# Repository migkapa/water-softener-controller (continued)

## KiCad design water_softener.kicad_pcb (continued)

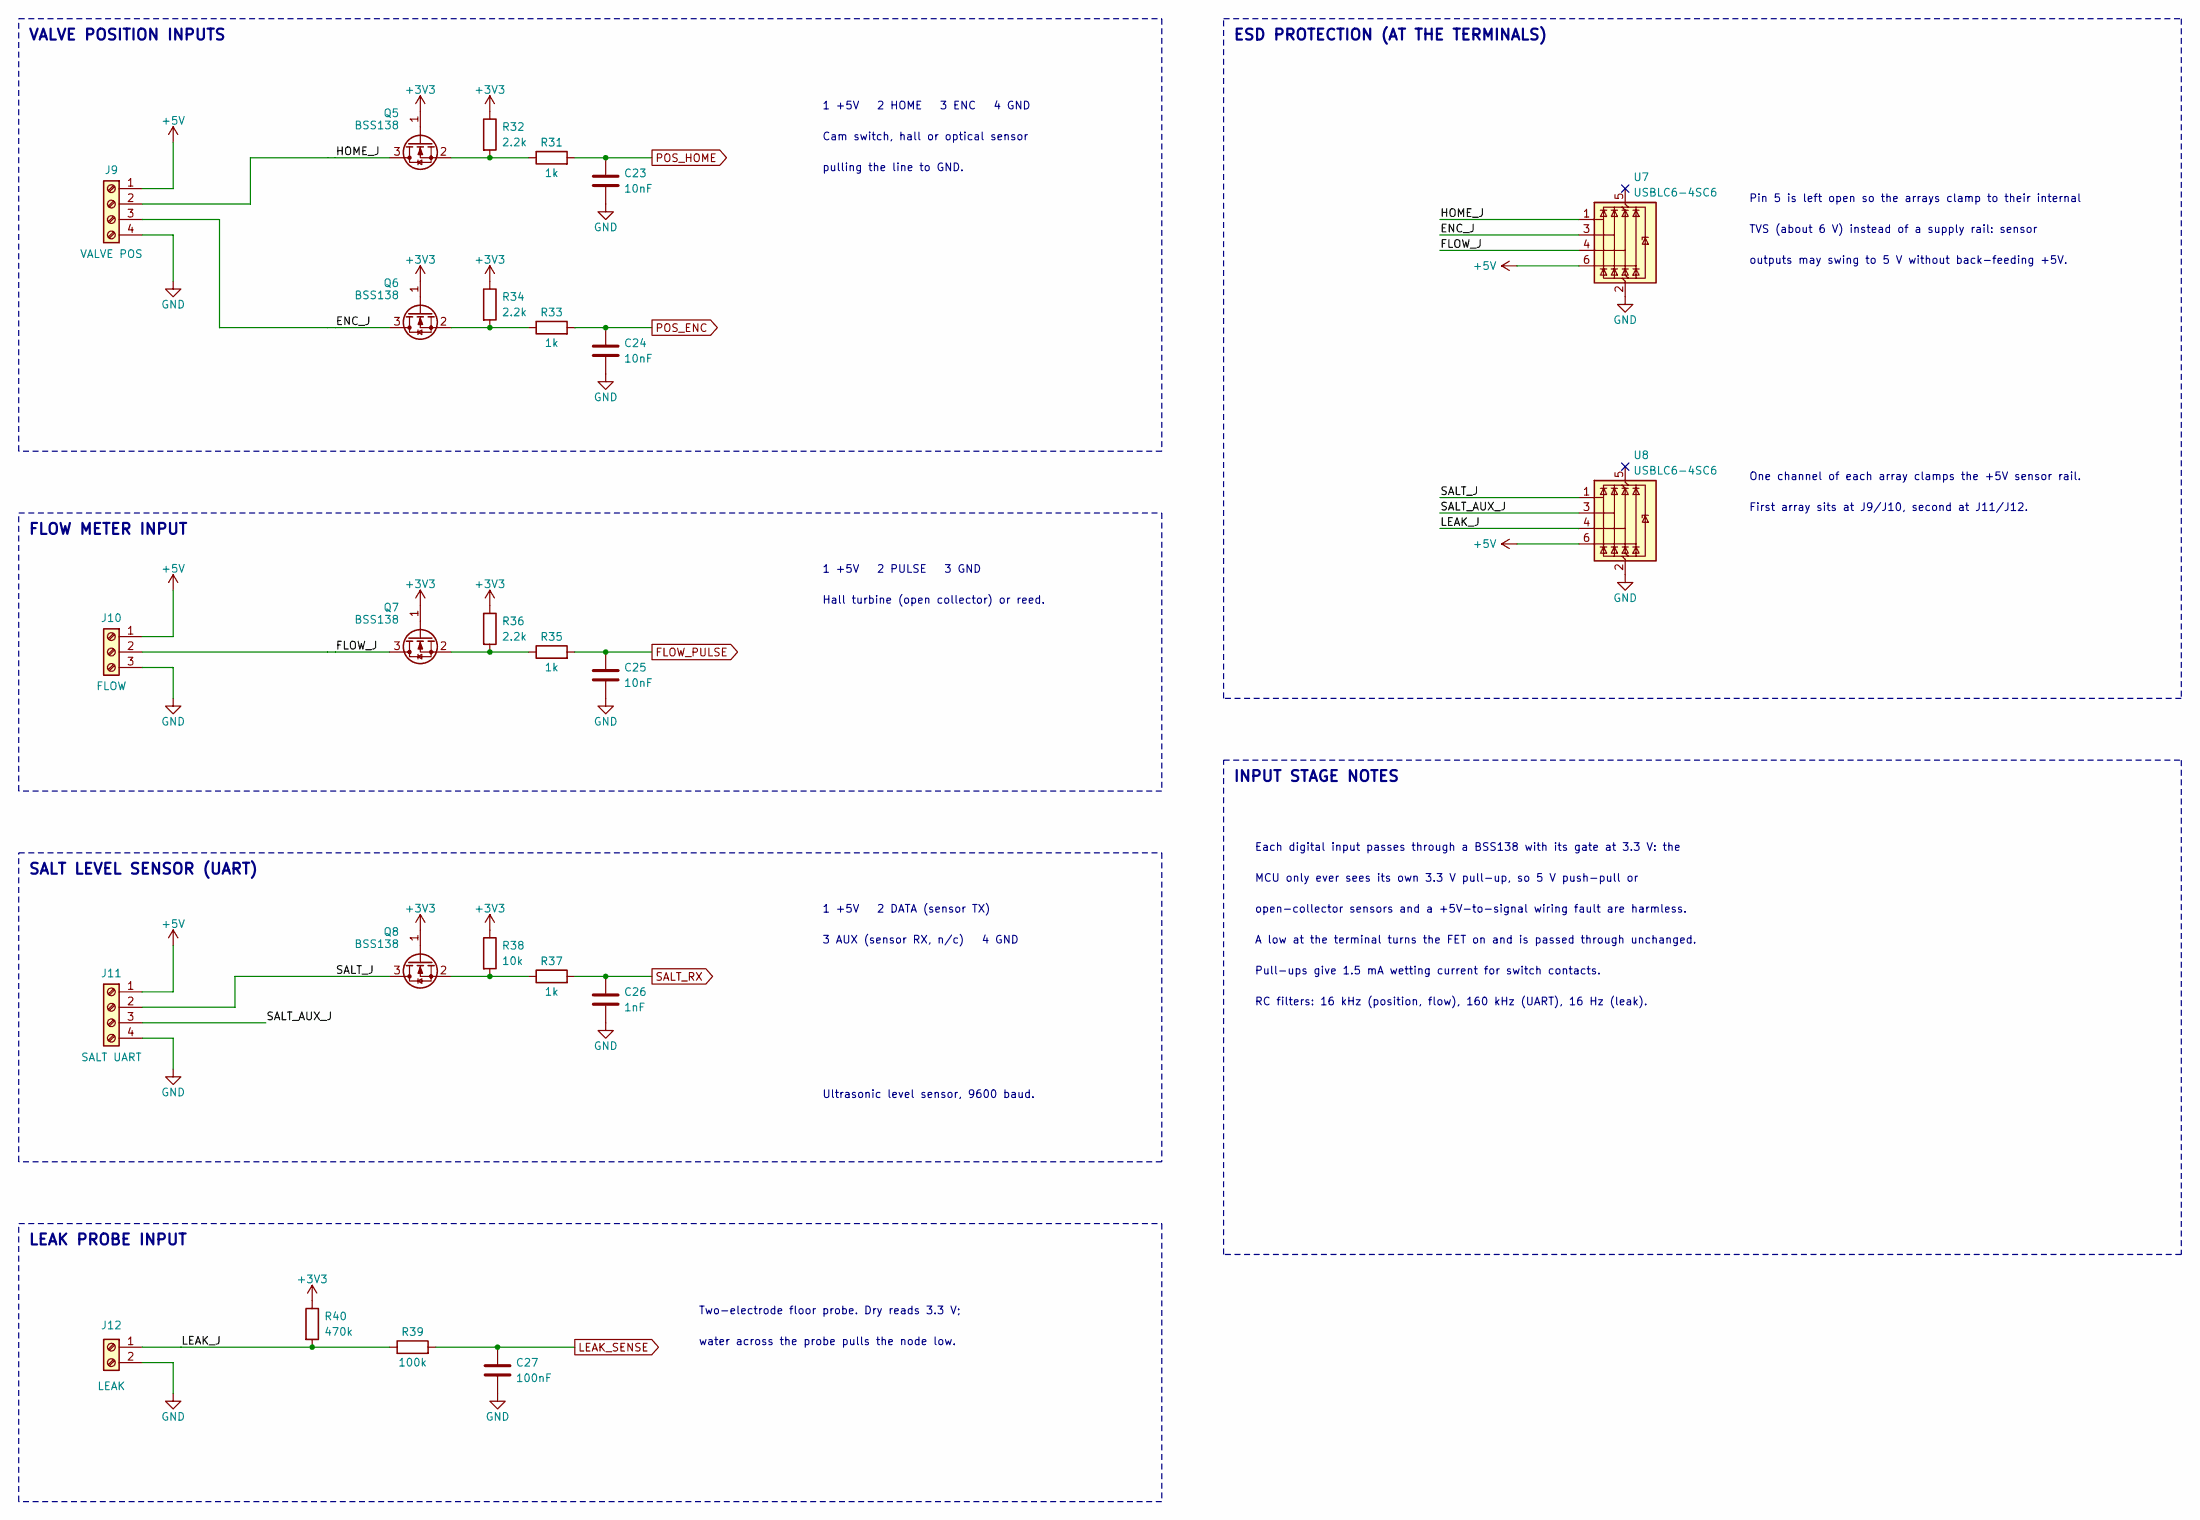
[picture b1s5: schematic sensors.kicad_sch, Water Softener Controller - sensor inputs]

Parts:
C23, C24, C25: 10nF; C_0603_1608Metric; Rating 50 V X7R
C26: 1nF; C_0603_1608Metric; Rating 50 V X7R
C27: 100nF; C_0603_1608Metric; Rating 50 V X7R
J9: VALVE POS; PhoenixContact_MC_1,5_4-G-3.5_1x04_P3.50mm_Horizontal; MPN 1844236
J10: FLOW; PhoenixContact_MC_1,5_3-G-3.5_1x03_P3.50mm_Horizontal; MPN 1844223
J11: SALT UART; PhoenixContact_MC_1,5_4-G-3.5_1x04_P3.50mm_Horizontal; MPN 1844236
J12: LEAK; PhoenixContact_MC_1,5_2-G-3.5_1x02_P3.50mm_Horizontal; MPN 1844210
Q5, Q6, Q7, Q8: BSS138; SOT-23; MPN BSS138
R31, R33, R35, R37: 1k; R_0603_1608Metric; Rating 1% 0.1W
R32, R34, R36: 2.2k; R_0603_1608Metric; Rating 1% 0.1W
R38: 10k; R_0603_1608Metric; Rating 1% 0.1W
R39: 100k; R_0603_1608Metric; Rating 1% 0.1W
R40: 470k; R_0603_1608Metric; Rating 1% 0.1W
U7, U8: USBLC6-4SC6; SOT-23-6; MPN USBLC6-4SC6

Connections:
+3V3: Q5.1 (G), Q6.1 (G), Q7.1 (G), Q8.1 (G), R32.1, R34.1, R36.1, R38.1, R40.1; also elsewhere on the board
+5V: J9.1, J10.1, J11.1, U7.6 (I/O4), U8.6 (I/O4); also elsewhere on the board
/Sensors/ENC_J: J9.3, Q6.3 (D), U7.3 (I/O2)
/Sensors/FLOW_J: J10.2, Q7.3 (D), U7.4 (I/O3)
/Sensors/HOME_J: J9.2, Q5.3 (D), U7.1 (I/O1)
/Sensors/LEAK_J: J12.1, R39.1, R40.2, U8.4 (I/O3)
/Sensors/SALT_AUX_J: J11.3, U8.3 (I/O2)
/Sensors/SALT_J: J11.2, Q8.3 (D), U8.1 (I/O1)
FLOW_PULSE: C25.1, R35.2; also elsewhere on the board
GND: C23.2, C24.2, C25.2, C26.2, C27.2, J9.4, J10.3, J11.4, J12.2, U7.2 (GND), U8.2 (GND); also elsewhere on the board
LEAK_SENSE: C27.1, R39.2; also elsewhere on the board
unnamed: Q5.2 (S), R31.1, R32.2
unnamed: Q6.2 (S), R33.1, R34.2
unnamed: Q7.2 (S), R35.1, R36.2
unnamed: Q8.2 (S), R37.1, R38.2
POS_ENC: C24.1, R33.2; also elsewhere on the board
POS_HOME: C23.1, R31.2; also elsewhere on the board
SALT_RX: C26.1, R37.2; also elsewhere on the board

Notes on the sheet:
3 AUX (sensor RX, n/c) 4 GND
FLOW METER INPUT
INPUT STAGE NOTES
Pin 5 is left open so the arrays clamp to their internal
open-collector sensors and a +5V-to-signal wiring fault are harmless.
MCU only ever sees its own 3.3 V pull-up, so 5 V push-pull or
TVS (about 6 V) instead of a supply rail: sensor
VALVE POSITION INPUTS
Each digital input passes through a BSS138 with its gate at 3.3 V: the
1 +5V 2 HOME 3 ENC 4 GND
RC filters: 16 kHz (position, flow), 160 kHz (UART), 16 Hz (leak).
First array sits at J9/J10, second at J11/J12.
water across the probe pulls the node low.
A low at the terminal turns the FET on and is passed through unchanged.
Hall turbine (open collector) or reed.
1 +5V 2 PULSE 3 GND
Cam switch, hall or optical sensor
Ultrasonic level sensor, 9600 baud.
outputs may swing to 5 V without back-feeding +5V.
1 +5V 2 DATA (sensor TX)
ESD PROTECTION (AT THE TERMINALS)
One channel of each array clamps the +5V sensor rail.
Two-electrode floor probe. Dry reads 3.3 V;
pulling the line to GND.
LEAK PROBE INPUT
SALT LEVEL SENSOR (UART)
Pull-ups give 1.5 mA wetting current for switch contacts.

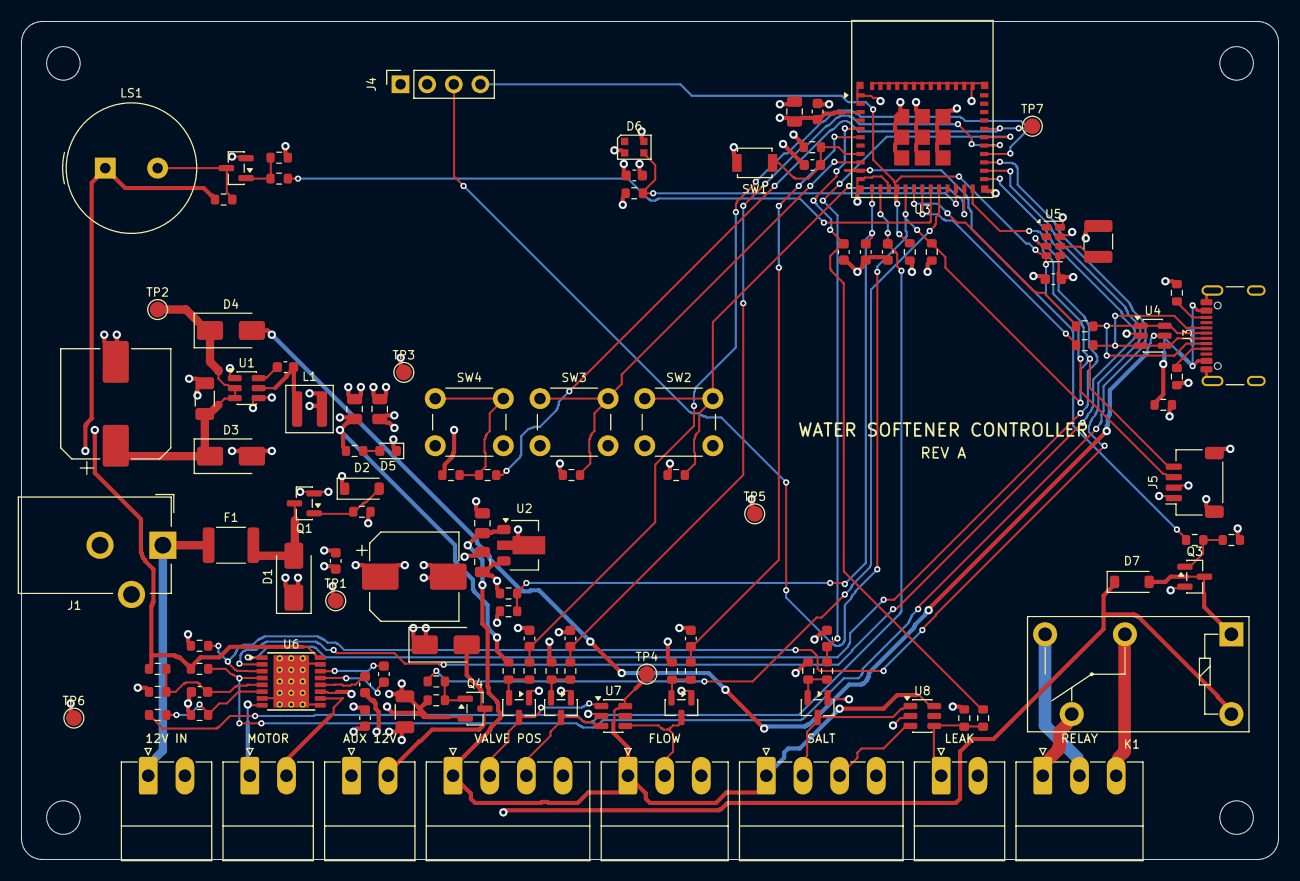
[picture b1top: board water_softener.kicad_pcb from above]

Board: 4 copper layers, 120.0 x 80.0 mm, 122 parts (0 on the bottom side), 67 nets.

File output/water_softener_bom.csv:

"Refs","Value","Rating","Footprint","Manufacturer","MPN","Qty"
"C1","220uF","25 V aluminium, 105 C","Capacitor_SMD:CP_Elec_8x10","Panasonic","EEE-FK1E221P","1"
"C2,C5,C10,C12,C14,C16,C17,C18,C19,C21,C27","100nF","50 V X7R","Capacitor_SMD:C_0603_1608Metric","","","11"
"C3","470uF","25 V aluminium, 105 C","Capacitor_SMD:CP_Elec_10x10","Panasonic","EEE-FK1E471P","1"
"C4,C20","10uF","25 V X7R","Capacitor_SMD:C_1206_3216Metric","","","2"
"C6,C7","22uF","10 V X5R","Capacitor_SMD:C_0805_2012Metric","","","2"
"C8,C9","1uF","50 V X7R","Capacitor_SMD:C_0805_2012Metric","","","2"
"C11","10uF","10 V X5R","Capacitor_SMD:C_0805_2012Metric","","","1"
"C13","1uF","16 V X7R","Capacitor_SMD:C_0603_1608Metric","","","1"
"C15","11mF","3.3 V EDLC","Capacitor_SMD:C_1210_3225Metric","Seiko Instruments","CPH3225A","1"
"C22","22nF","50 V X7R","Capacitor_SMD:C_0603_1608Metric","","","1"
"C23,C24,C25","10nF","50 V X7R","Capacitor_SMD:C_0603_1608Metric","","","3"
"C26","1nF","50 V X7R","Capacitor_SMD:C_0603_1608Metric","","","1"
"D1","SMAJ16CA","16 V standoff, 400 W, bidirectional","Diode_SMD:D_SMA","Littelfuse","SMAJ16CA","1"
"D2","BZT52C10","10 V 5%","Diode_SMD:D_SOD-123","Diodes Inc.","BZT52C10-7-F","1"
"D3,D4,D8","SS14","40 V 1 A Schottky","Diode_SMD:D_SMA","Vishay","SS14-E3/61T","3"
"D5","GREEN","","LED_SMD:LED_0603_1608Metric","Wurth Elektronik","150060GS75000","1"
"D6","WS2812B-2020","","LED_SMD:LED_WS2812B-2020_PLCC4_2.0x2.0mm","Worldsemi","WS2812B-2020 (V6)","1"
"D7","1N4148W","","Diode_SMD:D_SOD-123","Diodes Inc.","1N4148W-7-F","1"
"F1","1.5A / 24V","1.5 A hold, 3 A trip, 24 V","Fuse:Fuse_1812_4532Metric","Bourns","MF-MSMF150/24X-2","1"
"J1","12V DC IN","","Connector_BarrelJack:BarrelJack_CUI_PJ-102AH_Horizontal","CUI Devices","PJ-102AH","1"
"J2","12V IN (ALT)","","Connector_Phoenix_MC:PhoenixContact_MC_1,5_2-G-3.5_1x02_P3.50mm_Horizontal","Phoenix Contact","1844210","1"
"J3","USB-C","","Connector_USB:USB_C_Receptacle_GCT_USB4105-xx-A_16P_TopMnt_Horizontal","GCT","USB4105-GF-A","1"
"J4","OLED","","Connector_PinSocket_2.54mm:PinSocket_1x04_P2.54mm_Vertical","Generic","1x04 2.54 mm socket","1"
"J5","QWIIC","","Connector_JST:JST_SH_SM04B-SRSS-TB_1x04-1MP_P1.00mm_Horizontal","JST","SM04B-SRSS-TB","1"
"J6","VALVE MOTOR","","Connector_Phoenix_MC:PhoenixContact_MC_1,5_2-G-3.5_1x02_P3.50mm_Horizontal","Phoenix Contact","1844210","1"
"J7","RELAY","","Connector_Phoenix_MC:PhoenixContact_MC_1,5_3-G-3.5_1x03_P3.50mm_Horizontal","Phoenix Contact","1844223","1"
"J8","AUX 12V OUT","","Connector_Phoenix_MC:PhoenixContact_MC_1,5_2-G-3.5_1x02_P3.50mm_Horizontal","Phoenix Contact","1844210","1"
"J9","VALVE POS","","Connector_Phoenix_MC:PhoenixContact_MC_1,5_4-G-3.5_1x04_P3.50mm_Horizontal","Phoenix Contact","1844236","1"
"J10","FLOW","","Connector_Phoenix_MC:PhoenixContact_MC_1,5_3-G-3.5_1x03_P3.50mm_Horizontal","Phoenix Contact","1844223","1"
"J11","SALT UART","","Connector_Phoenix_MC:PhoenixContact_MC_1,5_4-G-3.5_1x04_P3.50mm_Horizontal","Phoenix Contact","1844236","1"
"J12","LEAK","","Connector_Phoenix_MC:PhoenixContact_MC_1,5_2-G-3.5_1x02_P3.50mm_Horizontal","Phoenix Contact","1844210","1"
"K1","G5Q-14 DC12","12 V coil 33 mA, SPDT","Relay_THT:Relay_SPDT_Omron-G5Q-1","Omron","G5Q-14 DC12","1"
"L1","4.7uH","4.7 uH, Isat 4.5 A, 44 mOhm","Inductor_SMD:L_Coilcraft_XAL4030-XXX","Coilcraft","XAL4030-472MEC","1"
"LS1","PS1240","","Buzzer_Beeper:Buzzer_TDK_PS1240P02BT_D12.2mm_H6.5mm","TDK","PS1240P02BT","1"
"Q1","DMP3099L","-30 V, 65 mOhm, Vgs +/-20 V","Package_TO_SOT_SMD:SOT-23","Diodes Inc.","DMP3099L-7","1"
"Q2,Q3,Q5,Q6,Q7,Q8","BSS138","","Package_TO_SOT_SMD:SOT-23","onsemi","BSS138","6"
"Q4","AO3400A","","Package_TO_SOT_SMD:SOT-23","Alpha & Omega","AO3400A","1"
"R1,R3,R19,R39","100k","1% 0.1W","Resistor_SMD:R_0603_1608Metric","","","4"
"R2,R8,R31,R33,R35,R37","1k","1% 0.1W","Resistor_SMD:R_0603_1608Metric","","","6"
"R4","15k","1% 0.1W","Resistor_SMD:R_0603_1608Metric","","","1"
"R5,R6,R7,R9,R10,R17,R21,R24,R25,R26,R28,R30,R38","10k","1% 0.1W","Resistor_SMD:R_0603_1608Metric","","","13"
"R11,R12","22R","1% 0.1W","Resistor_SMD:R_0603_1608Metric","","","2"
"R13,R14","5.1k","1% 0.1W","Resistor_SMD:R_0603_1608Metric","","","2"
"R15,R16,R20,R32,R34,R36","2.2k","1% 0.1W","Resistor_SMD:R_0603_1608Metric","","","6"
"R18,R27,R29","100R","1% 0.1W","Resistor_SMD:R_0603_1608Metric","","","3"
"R22","30.1k","1% 0.1W","Resistor_SMD:R_0603_1608Metric","","","1"
"R23","2.49k","1% 0.1W","Resistor_SMD:R_0603_1608Metric","","","1"
"R40","470k","1% 0.1W","Resistor_SMD:R_0603_1608Metric","","","1"
"SW1","RESET","","Button_Switch_SMD:SW_SPST_B3U-1000P","Omron","B3U-1000P","1"
"SW2","SET / BOOT","","Button_Switch_THT:SW_PUSH_6mm","Omron","B3F-1000","1"
"SW3","UP","","Button_Switch_THT:SW_PUSH_6mm","Omron","B3F-1000","1"
"SW4","DOWN","","Button_Switch_THT:SW_PUSH_6mm","Omron","B3F-1000","1"
"U1","AP63203WU","","Package_TO_SOT_SMD:TSOT-23-6","Diodes Inc.","AP63203WU-7","1"
"U2","L78L05","","Package_TO_SOT_SMD:SOT-89-3","STMicroelectronics","L78L05ABUTR","1"
"U3","ESP32-C6-MINI-1-N4","","RF_Module:ESP32-C6-MINI-1","Espressif","ESP32-C6-MINI-1-N4","1"
"U4","USBLC6-2SC6","","Package_TO_SOT_SMD:SOT-23-6","STMicroelectronics","USBLC6-2SC6","1"
"U5","RV-3028-C7","","Package_SON:MicroCrystal_C7_SON-8_1.5x3.2mm_P0.9mm","Micro Crystal","RV-3028-C7 32.768kHz 1ppm TA QC","1"
"U6","DRV8876PWP","","Package_SO:HTSSOP-16-1EP_4.4x5mm_P0.65mm_EP3.4x5mm_Mask3x3mm_ThermalVias","Texas Instruments","DRV8876PWPR","1"
"U7,U8","USBLC6-4SC6","","Package_TO_SOT_SMD:SOT-23-6","STMicroelectronics","USBLC6-4SC6","2"

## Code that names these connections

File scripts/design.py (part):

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    b.block(88, 16, 150, 60, 'ESD PROTECTION (AT THE TERMINALS)')
    u = b.part('Power_Protection:USBLC6-4SC6', 'U', 114, 30, value='USBLC6-4SC6',
               fields=mpn('STMicroelectronics', 'USBLC6-4SC6'))
    for pin, name in (('1', 'HOME_J'), ('3', 'ENC_J'), ('4', 'FLOW_J')):
        p = u[pin]
        b.w(p, (102, p.y / U)); b.lb(name, 102, p.y / U)
    b.w(u['6'], (107, 32)); b.pw('+5V', 107, 32, rot=90)
    b.nc(u['5']); b.gnd(114, 34)
    u = b.part('Power_Protection:USBLC6-4SC6', 'U', 114, 48, value='USBLC6-4SC6',
               fields=mpn('STMicroelectronics', 'USBLC6-4SC6'))
    for pin, name in (('1', 'SALT_J'), ('3', 'SALT_AUX_J'), ('4', 'LEAK_J')):
        p = u[pin]
        b.w(p, (102, p.y / U)); b.lb(name, 102, p.y / U)
    b.w(u['6'], (107, 50)); b.pw('+5V', 107, 50, rot=90)
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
